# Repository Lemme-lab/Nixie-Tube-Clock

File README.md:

# Nixie-Tube-Clock
A Desktop Nixie Clock with 4 220V old style Nixie Tubes. Powered By an Arduino Mini and an RTC Clock. 

---

---

---

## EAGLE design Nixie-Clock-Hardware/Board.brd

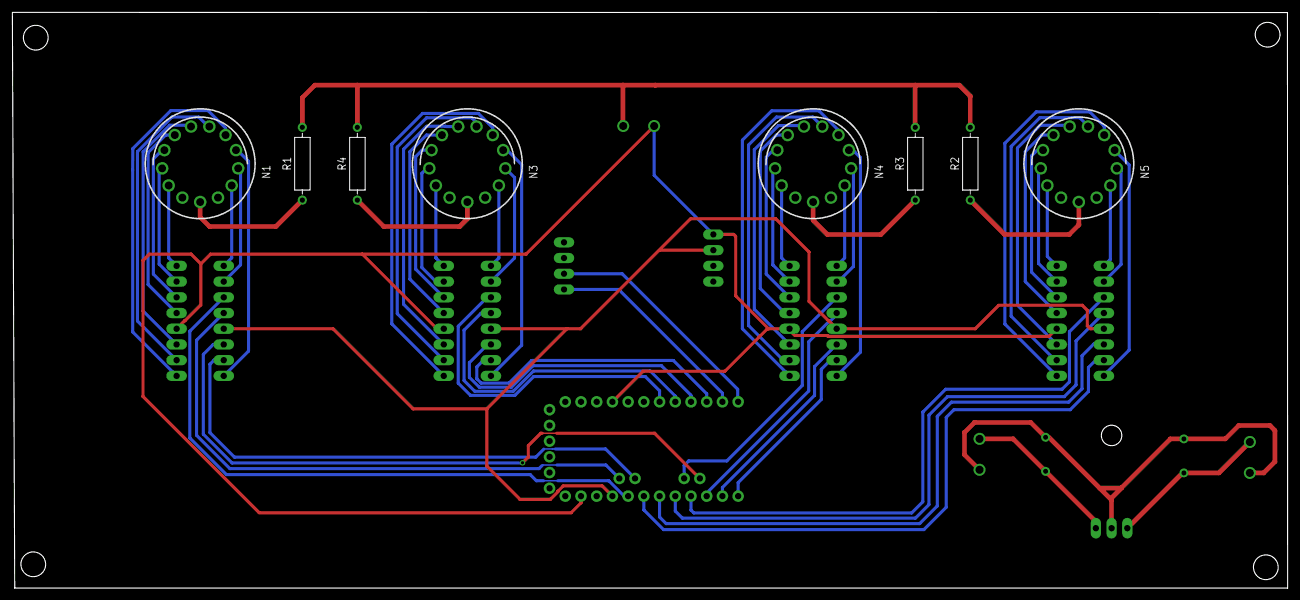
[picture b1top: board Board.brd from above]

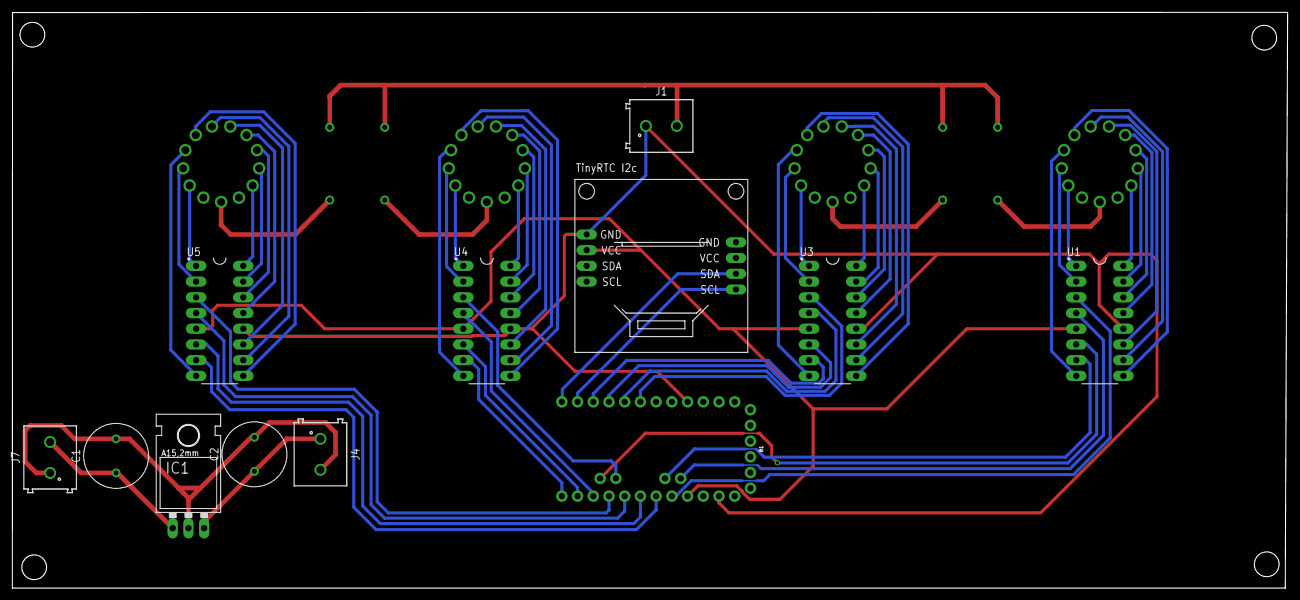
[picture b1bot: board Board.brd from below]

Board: 2 copper layers, 206.1 x 93.0 mm, 20 parts (12 on the bottom side), 68 nets.

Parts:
B1: ARDUINO_PRO_MINI
C1, C2: CAPRD550W60D1025H1250B
IC1: 78XXL
J1, J4, J7: 691213710002
N1, N3, N4, N5: IN-14
R1, R2, R3, R4: RESAD1176W63L850D250B
T1: TINYRTC
U1, U3, U4, U5: SN74141N; DIP762W46P254L2134H508Q16

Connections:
unnamed: N1.1, U1.16
unnamed: N1.2, U1.15
unnamed: N1.3, U1.14
unnamed: N1.4, U1.13
unnamed: N1.5, U1.11
unnamed: N1.6, U1.10
unnamed: N1.0, U1.1
unnamed: N1.9, U1.2
unnamed: N1.7, U1.9
unnamed: N1.8, U1.8
unnamed: J1.2, R1.2, R2.2, R3.2, R4.2
unnamed: N1.A, R1.1
unnamed: N3.A, R4.1
unnamed: B1.11, T1.1
unnamed: B1.12, T1.2
unnamed: B1.4, B1.23, J1.1, T1.5, U1.12, U3.12, U4.12, U5.12
unnamed: B1.A5, U1.4
unnamed: B1.10, U3.7
unnamed: B1.A4, U1.7
unnamed: B1.A6, U1.6
unnamed: N3.1, U3.16
unnamed: N3.2, U3.15
unnamed: N3.3, U3.14
unnamed: N3.4, U3.13
unnamed: N3.5, U3.11
unnamed: N3.6, U3.10
unnamed: N3.0, U3.1
unnamed: N3.9, U3.2
unnamed: N3.7, U3.9
unnamed: N3.8, U3.8
unnamed: B1.15, U4.4
unnamed: N4.A, R3.1
unnamed: N4.1, U4.16
unnamed: N4.2, U4.15
unnamed: N4.3, U4.14
unnamed: N4.4, U4.13
unnamed: N4.5, U4.11
unnamed: N4.6, U4.10
unnamed: N4.0, U4.1
unnamed: N4.9, U4.2
unnamed: C1.1, IC1.IN, J7.2
unnamed: C1.2, C2.2, IC1.GND, J4.2, J7.1
unnamed: C2.1, IC1.OUT, J4.1
unnamed: B1.9, U3.6
unnamed: B1.8, U3.4
unnamed: B1.7, U3.3
unnamed: B1.21, T1.6, U1.5, U3.5, U4.5, U5.5
unnamed: B1.13, U4.7
unnamed: B1.14, U4.6
unnamed: B1.A7, U4.3
unnamed: B1.17, U5.4
unnamed: B1.19, U5.7
unnamed: B1.18, U5.6
unnamed: B1.16, U5.3
unnamed: B1.20, U1.3
unnamed: N4.7, U4.9
unnamed: N4.8, U4.8
unnamed: N5.A, R2.1
unnamed: N5.1, U5.16
unnamed: N5.2, U5.15
unnamed: N5.3, U5.14
unnamed: N5.4, U5.13
unnamed: N5.5, U5.11
unnamed: N5.6, U5.10
unnamed: N5.0, U5.1
unnamed: N5.9, U5.2
unnamed: N5.7, U5.9
unnamed: N5.8, U5.8

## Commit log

2021-11-14 init

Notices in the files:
parts and their libraries:
Wurth_Connectors_WR-TBL Rising Cage Clam: Copyright: Würth Elektronik
SparkFun-Boards: Licensing: Creative Commons ShareAlike 4.0 International - https://creativecommons.org/licenses/by-sa/4.0
